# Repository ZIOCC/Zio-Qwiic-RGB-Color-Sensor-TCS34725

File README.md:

# Zio Qwiic RGB Color Sensor (TCS34725)

> This product can be available for purchase [here](https://www.smart-prototyping.com/Zio-Qwiic-RGB-Color-Sensor-TCS34725).

#### Description

The Qwiic Color Sensor board features one of the best color sensor on the market to monitor a specific color value and light sensing.

The board features a TCS34725 with I2C interface and minimizes the IR and UV spectral to make the color measurements as accurate as possible. 
 
The high sensitivity, IR blocking filter and wide dynamic range (3.8M:1) with adjustable integration time and gain make the sensor a great solution for use under different light conditions and attenuating materials. 
 
Finally, we specified a nice neutral 4150°K temperature LED with a MOSFET driver onboard to illuminate what you're trying to sense. The LED can be easily turned on or off by any logic level output.
 
The Zio Qwiic RGB Color Sensor uses the Qwiic connector for deasy chain with any Qwiic compatible boards. Just in case you would like to use this board without the Qwiic connector, we have incorporated header pins. As well as if you’d like to access the LED and INT pins.

#### Specification

* Operation Voltage: 3.3V
* Interface: I2C (address 0x29)
* Dimensions:18.1x25.5mm
* Weight:1.2g

#### Links

* [PCB Source File and Schematic](https://github.com/ZIOCC/Zio-Qwiic-RGB-Color-Sensor-TCS34725)
* [TCS34725 Datasheet](https://ams.com/documents/20143/36005/TCS3472_DS000390_2-00.pdf/)
* [Adafruit TCS34725 master Library](https://github.com/adafruit/Adafruit_TCS34725)

> ###### About Zio
> Zio is a new line of open sourced, compact, and grid layout boards, fully integrated for Arduino and Qwiic ecosystem. Designed ideally for wearables, robotics, small-space limitations or other on the go projects. Check out other awesome Zio products [here](https://www.smart-prototyping.com/Zio).

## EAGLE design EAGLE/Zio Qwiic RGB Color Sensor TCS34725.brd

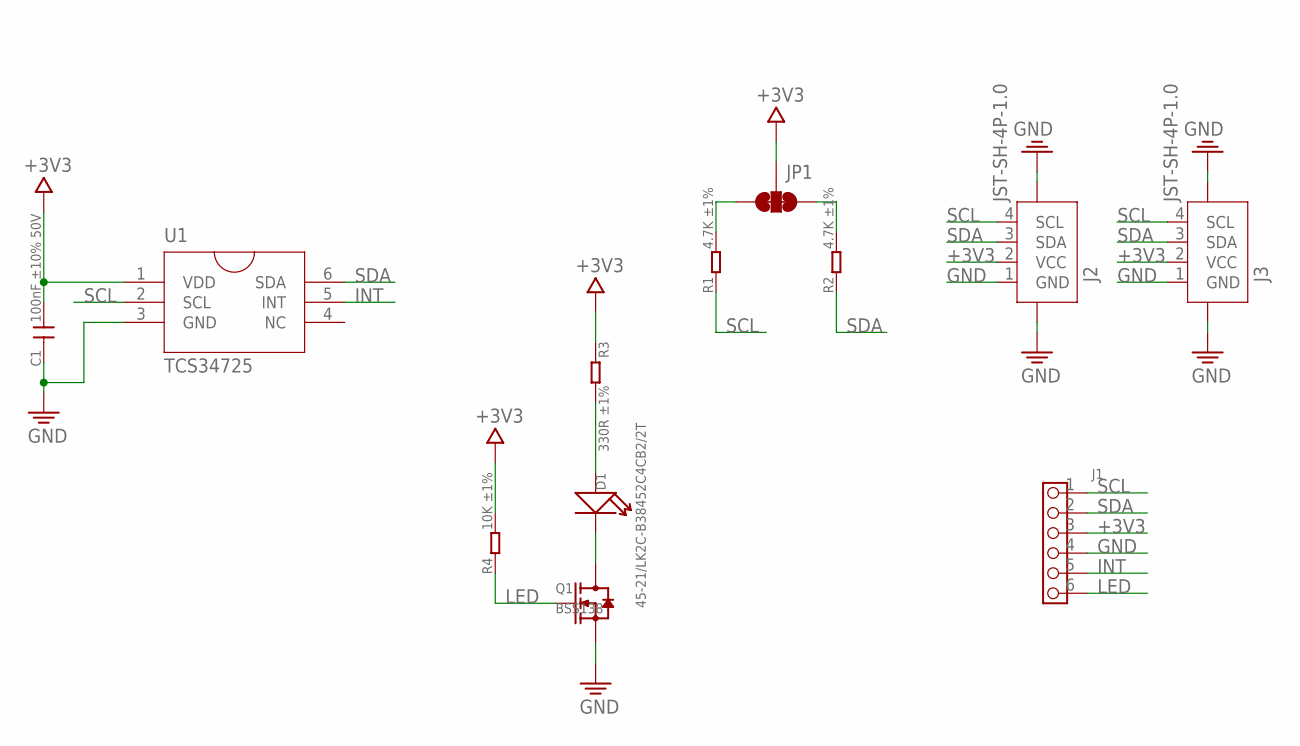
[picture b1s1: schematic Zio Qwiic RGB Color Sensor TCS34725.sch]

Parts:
C1: 100nF ±10% 50V; C0603
D1: 45-21/LK2C-B38452C4CB2/2T; EVERLIGHT_45-21
J1: HEADER-6P-60/35MIL; 6P-2.54-60/35MIL
J2, J3: JST-SH-4P-1.0; JST-SH-4P
JP1: SMT-JUMPER_3_2-NC_TRACE
Q1: BSS138; SOT23
R1, R2: 4.7K ±1%; R0603
R3: 330R ±1%; R0603
R4: 10K ±1%; R0603
U1: TCS34725; FN6_TCS3472

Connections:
+3V3: C1.2, J1.3, J2.2 (VCC), J3.2 (VCC), JP1.2, R3.1, R4.2, U1.1 (VDD)
GND: C1.1, J1.4, J2.1 (GND), J2.NC1 (5), J2.NC2 (6), J3.1 (GND), J3.NC1 (5), J3.NC2 (6), Q1.2 (S), U1.3 (GND)
INT: J1.5, U1.5 (INT)
LED: J1.6, Q1.1 (G), R4.1
unnamed: D1.A (+), R3.2
unnamed: D1.K (-), Q1.3 (D)
unnamed: JP1.3, R1.2
unnamed: JP1.1, R2.2
SCL: J1.1, J2.4 (SCL), J3.4 (SCL), R1.1, U1.2 (SCL)
SDA: J1.2, J2.3 (SDA), J3.3 (SDA), R2.1, U1.6 (SDA)

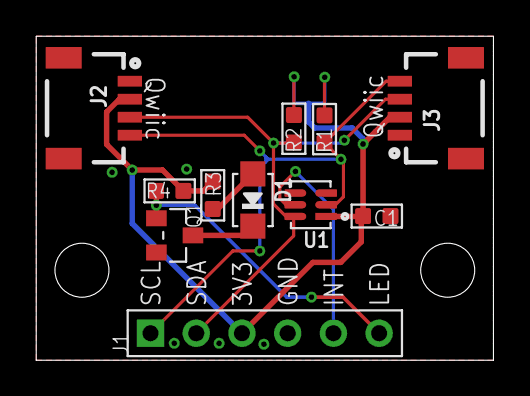
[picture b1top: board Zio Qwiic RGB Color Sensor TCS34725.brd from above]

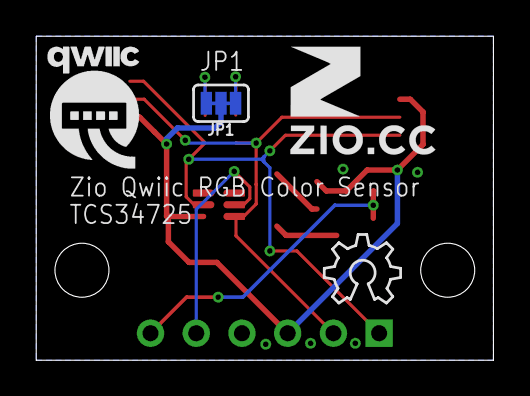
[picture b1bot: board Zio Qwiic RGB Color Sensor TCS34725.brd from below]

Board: 2 copper layers, 25.4 x 18.0 mm, 15 parts (4 on the bottom side), 10 nets.

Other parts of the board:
U$5: 6MM
U$6: OSHW_6X150_NOTEXT
U$7: QWIIC-LOGO-MEDIUM
